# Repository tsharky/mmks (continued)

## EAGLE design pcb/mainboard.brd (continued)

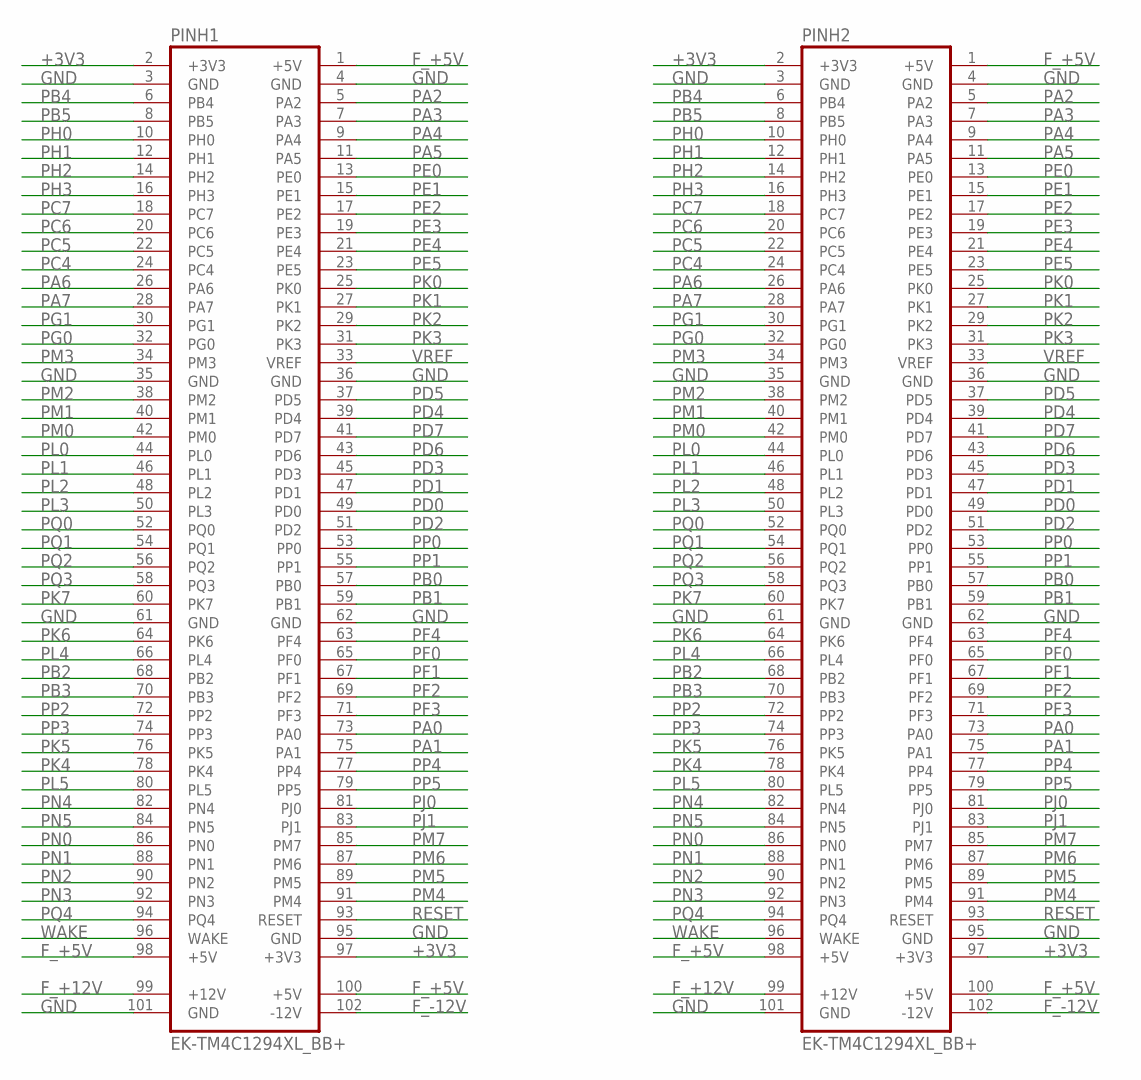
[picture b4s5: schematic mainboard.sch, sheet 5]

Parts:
PINH1, PINH2: EK-TM4C1294XL_BB+

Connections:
+3V3: PINH1.2 (+3V3), PINH1.97 (+3V3), PINH2.2 (+3V3), PINH2.97 (+3V3); also elsewhere on the board
F_+5V: PINH1.1 (+5V), PINH1.98 (+5V), PINH1.100 (+5V), PINH2.1 (+5V), PINH2.98 (+5V), PINH2.100 (+5V); also elsewhere on the board
F_+12V: PINH1.99 (+12V), PINH2.99 (+12V); also elsewhere on the board
F_-12V: PINH1.102 (-12V), PINH2.102 (-12V); also elsewhere on the board
GND: PINH1.3 (GND), PINH1.4 (GND), PINH1.35 (GND), PINH1.36 (GND), PINH1.61 (GND), PINH1.62 (GND), PINH1.95 (GND), PINH1.101 (GND), PINH2.3 (GND), PINH2.4 (GND), PINH2.35 (GND), PINH2.36 (GND), PINH2.61 (GND), PINH2.62 (GND), PINH2.95 (GND), PINH2.101 (GND); also elsewhere on the board
PA0: PINH1.73 (PA0), PINH2.73 (PA0); also elsewhere on the board
PA1: PINH1.75 (PA1), PINH2.75 (PA1); also elsewhere on the board
PA2: PINH1.5 (PA2), PINH2.5 (PA2); also elsewhere on the board
PA3: PINH1.7 (PA3), PINH2.7 (PA3); also elsewhere on the board
PA4: PINH1.9 (PA4), PINH2.9 (PA4); also elsewhere on the board
PA5: PINH1.11 (PA5), PINH2.11 (PA5); also elsewhere on the board
PA6: PINH1.26 (PA6), PINH2.26 (PA6); also elsewhere on the board
PA7: PINH1.28 (PA7), PINH2.28 (PA7); also elsewhere on the board
PB0: PINH1.57 (PB0), PINH2.57 (PB0); also elsewhere on the board
PB1: PINH1.59 (PB1), PINH2.59 (PB1); also elsewhere on the board
PB2: PINH1.68 (PB2), PINH2.68 (PB2); also elsewhere on the board
PB3: PINH1.70 (PB3), PINH2.70 (PB3); also elsewhere on the board
PB4: PINH1.6 (PB4), PINH2.6 (PB4); also elsewhere on the board
PB5: PINH1.8 (PB5), PINH2.8 (PB5); also elsewhere on the board
PC4: PINH1.24 (PC4), PINH2.24 (PC4); also elsewhere on the board
PC5: PINH1.22 (PC5), PINH2.22 (PC5); also elsewhere on the board
PC6: PINH1.20 (PC6), PINH2.20 (PC6); also elsewhere on the board
PC7: PINH1.18 (PC7), PINH2.18 (PC7); also elsewhere on the board
PD0: PINH1.49 (PD0), PINH2.49 (PD0); also elsewhere on the board
PD1: PINH1.47 (PD1), PINH2.47 (PD1); also elsewhere on the board
PD2: PINH1.51 (PD2), PINH2.51 (PD2); also elsewhere on the board
PD3: PINH1.45 (PD3), PINH2.45 (PD3); also elsewhere on the board
PD4: PINH1.39 (PD4), PINH2.39 (PD4); also elsewhere on the board
PD5: PINH1.37 (PD5), PINH2.37 (PD5); also elsewhere on the board
PD6: PINH1.43 (PD6), PINH2.43 (PD6); also elsewhere on the board
PD7: PINH1.41 (PD7), PINH2.41 (PD7); also elsewhere on the board
PE0: PINH1.13 (PE0), PINH2.13 (PE0); also elsewhere on the board
PE1: PINH1.15 (PE1), PINH2.15 (PE1); also elsewhere on the board
PE2: PINH1.17 (PE2), PINH2.17 (PE2); also elsewhere on the board
PE3: PINH1.19 (PE3), PINH2.19 (PE3); also elsewhere on the board
PE4: PINH1.21 (PE4), PINH2.21 (PE4); also elsewhere on the board
PE5: PINH1.23 (PE5), PINH2.23 (PE5); also elsewhere on the board
PF0: PINH1.65 (PF0), PINH2.65 (PF0); also elsewhere on the board
PF1: PINH1.67 (PF1), PINH2.67 (PF1); also elsewhere on the board
PF2: PINH1.69 (PF2), PINH2.69 (PF2); also elsewhere on the board
PF3: PINH1.71 (PF3), PINH2.71 (PF3); also elsewhere on the board
PF4: PINH1.63 (PF4), PINH2.63 (PF4); also elsewhere on the board
PG0: PINH1.32 (PG0), PINH2.32 (PG0); also elsewhere on the board
PG1: PINH1.30 (PG1), PINH2.30 (PG1); also elsewhere on the board
PH0: PINH1.10 (PH0), PINH2.10 (PH0); also elsewhere on the board
PH1: PINH1.12 (PH1), PINH2.12 (PH1); also elsewhere on the board
PH2: PINH1.14 (PH2), PINH2.14 (PH2); also elsewhere on the board
PH3: PINH1.16 (PH3), PINH2.16 (PH3); also elsewhere on the board
PJ0: PINH1.81 (PJ0), PINH2.81 (PJ0); also elsewhere on the board
PJ1: PINH1.83 (PJ1), PINH2.83 (PJ1); also elsewhere on the board
PK0: PINH1.25 (PK0), PINH2.25 (PK0); also elsewhere on the board
PK1: PINH1.27 (PK1), PINH2.27 (PK1); also elsewhere on the board
PK2: PINH1.29 (PK2), PINH2.29 (PK2); also elsewhere on the board
PK3: PINH1.31 (PK3), PINH2.31 (PK3); also elsewhere on the board
PK4: PINH1.78 (PK4), PINH2.78 (PK4); also elsewhere on the board
PK5: PINH1.76 (PK5), PINH2.76 (PK5); also elsewhere on the board
PK6: PINH1.64 (PK6), PINH2.64 (PK6); also elsewhere on the board
PK7: PINH1.60 (PK7), PINH2.60 (PK7); also elsewhere on the board
PL0: PINH1.44 (PL0), PINH2.44 (PL0); also elsewhere on the board
PL1: PINH1.46 (PL1), PINH2.46 (PL1); also elsewhere on the board
PL2: PINH1.48 (PL2), PINH2.48 (PL2); also elsewhere on the board
PL3: PINH1.50 (PL3), PINH2.50 (PL3); also elsewhere on the board
PL4: PINH1.66 (PL4), PINH2.66 (PL4); also elsewhere on the board
PL5: PINH1.80 (PL5), PINH2.80 (PL5); also elsewhere on the board
PM0: PINH1.42 (PM0), PINH2.42 (PM0); also elsewhere on the board
PM1: PINH1.40 (PM1), PINH2.40 (PM1); also elsewhere on the board
PM2: PINH1.38 (PM2), PINH2.38 (PM2); also elsewhere on the board
PM3: PINH1.34 (PM3), PINH2.34 (PM3); also elsewhere on the board
PM4: PINH1.91 (PM4), PINH2.91 (PM4); also elsewhere on the board
PM5: PINH1.89 (PM5), PINH2.89 (PM5); also elsewhere on the board
PM6: PINH1.87 (PM6), PINH2.87 (PM6); also elsewhere on the board
PM7: PINH1.85 (PM7), PINH2.85 (PM7); also elsewhere on the board
PN0: PINH1.86 (PN0), PINH2.86 (PN0); also elsewhere on the board
PN1: PINH1.88 (PN1), PINH2.88 (PN1); also elsewhere on the board
PN2: PINH1.90 (PN2), PINH2.90 (PN2); also elsewhere on the board
PN3: PINH1.92 (PN3), PINH2.92 (PN3); also elsewhere on the board
PN4: PINH1.82 (PN4), PINH2.82 (PN4); also elsewhere on the board
PN5: PINH1.84 (PN5), PINH2.84 (PN5); also elsewhere on the board
PP0: PINH1.53 (PP0), PINH2.53 (PP0); also elsewhere on the board
PP1: PINH1.55 (PP1), PINH2.55 (PP1); also elsewhere on the board
PP2: PINH1.72 (PP2), PINH2.72 (PP2); also elsewhere on the board
PP3: PINH1.74 (PP3), PINH2.74 (PP3); also elsewhere on the board
PP4: PINH1.77 (PP4), PINH2.77 (PP4); also elsewhere on the board
PP5: PINH1.79 (PP5), PINH2.79 (PP5); also elsewhere on the board
PQ0: PINH1.52 (PQ0), PINH2.52 (PQ0); also elsewhere on the board
PQ1: PINH1.54 (PQ1), PINH2.54 (PQ1); also elsewhere on the board
PQ2: PINH1.56 (PQ2), PINH2.56 (PQ2); also elsewhere on the board
PQ3: PINH1.58 (PQ3), PINH2.58 (PQ3); also elsewhere on the board
PQ4: PINH1.94 (PQ4), PINH2.94 (PQ4); also elsewhere on the board
RESET: PINH1.93 (RESET), PINH2.93 (RESET); also elsewhere on the board
VREF: PINH1.33 (VREF), PINH2.33 (VREF); also elsewhere on the board
WAKE: PINH1.96 (WAKE), PINH2.96 (WAKE); also elsewhere on the board

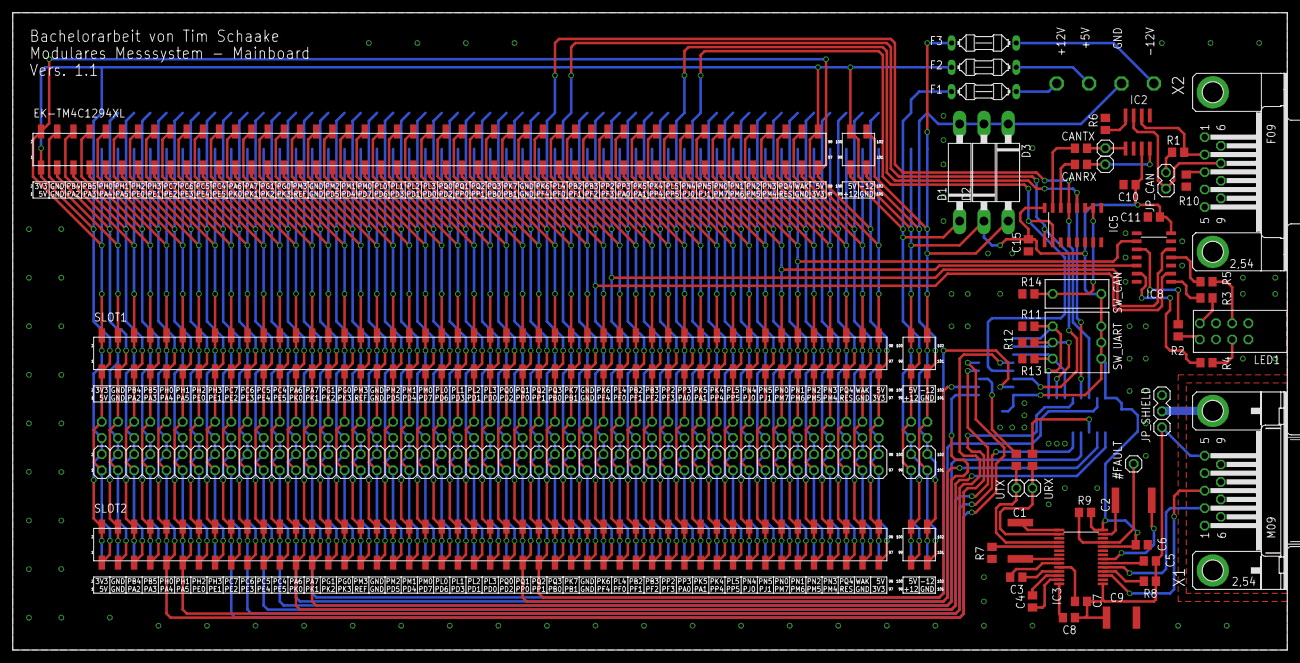
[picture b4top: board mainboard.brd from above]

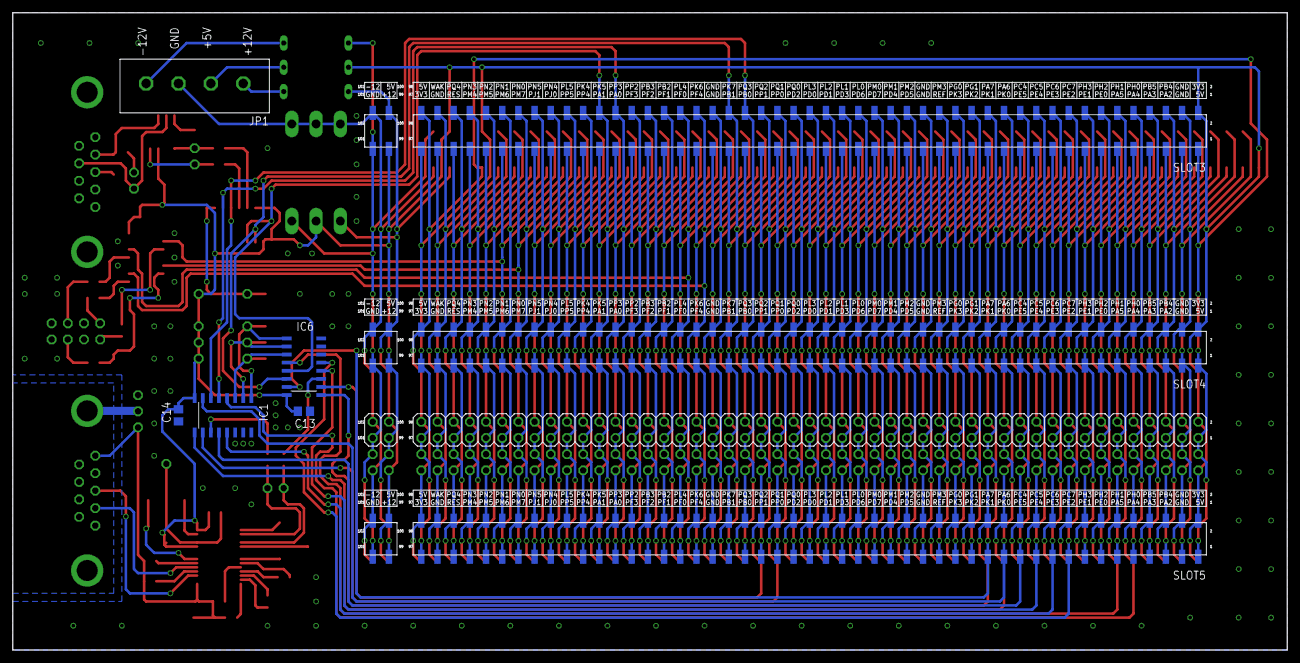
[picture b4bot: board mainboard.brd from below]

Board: 2 copper layers, 200.0 x 100.0 mm, 65 parts (9 on the bottom side), 138 nets.

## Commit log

2020-03-10 Initial project files
2020-04-13 Create LICENSE
2020-04-14 Project changes
    * New compiler version
    * Project formatter config
    * Apply formatter on main.cpp
    * MIT license
2020-04-16 First attempt for modern and clean code
2020-04-17 RS232 communication test
2020-04-18 Ignore .launches/ directory
2020-04-18 Optimize uart and add class for leds
2020-04-18 Remove unnecessary code composer studio files
2020-04-18 Add can communicaiton
